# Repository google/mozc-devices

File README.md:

Circuit diagrams and firmware source code for Gboard DIY keyboards, previously
known as Google Japanese Input / Gboard April Fools.

This is not an officially supported Google product.

# Products

Please refer to the README in each directory for more details.

<table>
<tr>
<td>

[Google 日本語入力 ドラムセットバージョン](https://archive.google/drumsetkeyboard/)<br>
[Google Japanese Input Drum set version](https://archive.google/drumsetkeyboard/)

変換の煩わしさを感じさせない思いどおりの日本語入力を提供します。

- [Announce](https://blog.google/intl/ja-jp/products/android-chrome-play/2010_04_google/)
- Release date: Apr 1, 2010
- Source: Not open source

</td>
<td>

[Google 日本語入力 モールスバージョン](http://www.google.co.jp/ime/-.-.html)<br>
[Google Japanese Input Morse version](http://www.google.co.jp/ime/-.-.html)

モールス符号で思いどおりの日本語入力

- [Promotional video](https://www.youtube.com/watch?v=u5AYb778pwA)
- [Announce](https://japan.googleblog.com/2012/04/google.html)
- [Technical details](http://googledevjp.blogspot.jp/2012/06/google.html)
- Release date: Apr 1, 2012
- Source: [/third_party/mozc-morse](./third_party/mozc-morse)

</td>
</tr>
<tr>
<td>

[Google 日本語入力 パタパタバージョン](http://www.google.co.jp/ime/patapata/)<br>
[Google Japanese Input Patapata version](http://www.google.co.jp/ime/patapata/)

もう、なにも覚える必要はありません。
押して離すだけの日本語入力。

- [Promotional video](https://www.youtube.com/watch?v=HzUDAaYMNsA)
- [Announce](https://japan.googleblog.com/2013/04/google-patapata.html)
- [Technical details](http://googledevjp.blogspot.jp/2013/10/google.html)
- Release date: Apr 1, 2013
- Source: [/third_party/mozc-flap](./third_party/mozc-flap)

</td>
<td>

[Google 日本語入力 マジックハンドバージョン](https://archive.google/ime/m9/)<br>
[Google Japanese Input Magic hand version](https://archive.google/ime/m9/)

マジックハンドでらくらく入力

- [Promotional video](https://www.youtube.com/watch?v=0u1zoaJYAmw)
- [Announce](https://blog.google/intl/ja-jp/products/android-chrome-play/2014_04_m9/)
- Release date: Apr 1, 2014
- Source: Not open source

</td>
</tr>
<tr>
<td>

[Google 日本語入力 ピロピロバージョン](https://www.google.co.jp/ime/___o/)<br>
[Google Japanese Input Piropiro version](https://www.google.co.jp/ime/___o/)

もうキーはいらない

- [Promotional video](https://www.youtube.com/watch?v=gAgOnQqyDz0)
- [Announce](https://japan.googleblog.com/2015/04/piropiro.html)
- Release date: Apr 1, 2015
- Source: [/mozc-piropiro](./mozc-piropiro)

</td>
<td>

[Google 日本語入力 物理フリックバージョン](https://www.google.co.jp/ime/furikku/)<br>
[Google Japanese Input Physical Flick version](https://www.google.co.jp/ime/furikku/)

さわれるフリック

- [Promotional video](https://www.youtube.com/watch?v=5LI1PysAlkU)
- [Announce](https://japan.googleblog.com/2016/04/furikku.html)
- Release date: Apr 1, 2016
- Source: [/mozc-furikku](./mozc-furikku)

</td>
</tr>
<tr>
<td>

[日本語入力 プチプチバージョン](https://landing.google.co.jp/ime/ooooo/)<br>
[Google Japanese Input Puchi Puchi version](https://landing.google.co.jp/ime/ooooo/)

空気のように、軽やかな入力。

- [Promotional video](https://www.youtube.com/watch?v=RkJZDvHMyTA)
- [Announce](https://japan.googleblog.com/2017/04/ooooo.html)
- Release date: Apr 1, 2017
- Source: [/third_party/mozc-puchi](./third_party/mozc-puchi)

</td>
<td>

[Gboard 物理手書きバージョン](https://landing.google.co.jp/tegaki/)<br>
[Gboard Physical Handwriting version](https://landing.google.co.jp/tegaki/)

新しいタイプの手書き入力。

- [Promotional video](https://www.youtube.com/watch?v=guJnFY1R4I0)
- [Announce](https://japan.googleblog.com/2018/04/tegaki.html)
- [Technical details](https://developers-jp.googleblog.com/2018/04/tegaki.html)
- Release date: Apr 1, 2018
- Source: [/mozc-nazoru](./mozc-nazoru)

</td>
</tr>
<tr>
<td>

[Gboard スプーン曲げバージョン](https://landing.google.co.jp/---o/)<br>
[Gboard Spoon Bending version](https://landing.google.co.jp/---o/)

タネも仕掛けもない、柔軟な入力。

- [Promotional video](https://www.youtube.com/watch?v=DeJY5d14qKs)
- [Announce](https://japan.googleblog.com/2019/04/mageru.html)
- Release date: Apr 1, 2019
- Source:
  - [/mozc-mageru](./mozc-mageru) for firmware, schematics, and PCB layout.
  - [/third_party/mozc-mageru](./third_party/mozc-mageru) for 3D model.

</td>
<td>

[Gboard 湯呑みバージョン](https://g.co/yunomi/)<br>
[Gboard yunomi version](https://g.co/yunomi/)

もう、おすしかない。

- [Promotional video](https://www.youtube.com/watch?v=20pC05yisRM)
- [Announce](https://japan.googleblog.com/2021/10/gboard.html)
- Release date: Oct 1, 2021
- Source: [/mozc-yunomi](./mozc-yunomi)

</td>
</tr>
<tr>
<td>

[Gboard 棒バージョン](https://g.co/____)<br>
[Gboard bar version](https://g.co/____)

キーの次はボーです。

- [Promotional video](https://www.youtube.com/watch?v=9G3DWHf1xX0)
- [Announce](https://japan.googleblog.com/2022/10/gboard-2022.html)
- Release date: Oct 1, 2022
- Source: [/mozc-bar](./mozc-bar)

</td>
<td>

[Gboard 帽バージョン](https://g.co/CAPS)<br>
[Gboard CAPS version](https://g.co/CAPS)

入力は、帽険だ。

- [Promotional video](https://www.youtube.com/watch?v=6vib77CUxNM)
- [Announce](https://japan.googleblog.com/2023/10/caps.html)
- Release date: Oct 1, 2023
- Source: [/mozc-caps](./mozc-caps)

</td>
</tr>
<tr>
<td>

[Gboard 両面バージョン](https://g.co/double-sided)<br>
[Gboard double sided version](https://g.co/double-sided)

表面かと思ったら裏面でした。

- [Promotional video](https://www.youtube.com/watch?v=EHqPrHTN1dU)
- [Announce](https://blog.google/intl/ja-jp/products/android-chrome-play/gboard-2024)
- Release date: Oct 1, 2024
- Source: [/mozc-doublesided](./mozc-doublesided)

</td>
<td>

[Gboard ダイヤルバージョン](./mozc-dial/README_ja.md)<br>
[Gboard Dial Version](./mozc-dial)

まるくおさめました。

- [Promotional video](https://youtu.be/BgdWyD0cBx4)
- [Announce](https://blog.google/intl/ja-jp/products/android-chrome-play/gboard-2025)
- Release date: Oct 1, 2025
- Source: [/mozc-dial](./mozc-dial)

</td>
</tr>
<tr>
<td>

[Gboard くるくる バージョン](./mozc-conveyorbelt/README_ja.md)<br>
[Gboard Conveyor Belt version](./mozc-conveyorbelt)

流れるような文字入力を

- [Promotional video](https://www.youtube.com/watch?v=DAn34l_YrUM)
- [Announce](https://blog.google/intl/ja-jp/products/android-chrome-play/gboard-2026/)
- Release date: Oct 1, 2026
- Source: [/mozc-conveyorbelt](./mozc-conveyorbelt)

</td>
<td>
</td>
</tr>
</table>

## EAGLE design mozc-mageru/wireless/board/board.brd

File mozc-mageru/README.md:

# Gboard Spoon Bending Version

This contains programs, schematics and board layouts for Gboard Spoon Bending Version, which was released on **Apr 1, 2019**.

This is not an officially supported Google product.

# Contents

Directory structure is as follows.

- wireless/
  - firmware/
    - Firmware for the wireless version. (coming soon)
  - board/
    - Schematic and PCB layout made by EAGLE.
- wired/
  - firmware/
    - Arduino sketch for the wired version.
- ../third_party/mozc-mageru/spoon_stl/
   - Spoon shape data for 3D printing.

# Wired Version

## The spoon

Print the spoon under /third_party/mozc-mageru/spoon_stl/ using a 3D printer.
This is an example design of a flexible spoon that has a slot to embed a
flex sensor into.
We have tried it with PLA, but it will probably work with ABS as well.

## Electronic circuit

- Arduino Micro
- 22k-ohm resistor
- Flex sensor: FS-L-0055-253-ST (Spectra Symbol)

```
    Arduino Micro

         5V ---[22k ohm]-------+
                               |
         A5 -------------------+
                               |
        GND ---[Flex sensor]---+
```

## How to use the firmware

1. Open the sketch on Arduino IDE.
2. Choose "Arduino/Genuino Micro" in the [Tools]-[Board] menu.
3. If you are making Japanse-hiragana version, add ```#define JAPANESE_``` to the first line of the sketch
4. Upload to board.

## Sensor calibration

1. Open Serial Monitor.
2. Send '!' once to disable key output.
3. (the home position, which decides when to commit a character)
   Bend the sensor slightly and send '0'. Make sure the LED turns off when the spoon is not bent by external force.
4. (the position for the first letter)
   Bend the sensor slightly a bit more and send '1'.
5. (the position for the last letter)
   Bend the sensor to the end and send '2'.
6. Send 'w' to save the configuration to EEPROM.
7. Send '!' again to enable key output, or reset the device.

# Wireless Version

Coming soon.

# License

```
Licensed under the Apache License, Version 2.0 (the "License"); you may
not use this file except in compliance with the License. You may obtain
a copy of the License at

    http://www.apache.org/licenses/LICENSE-2.0

Unless required by applicable law or agreed to in writing, software
distributed under the License is distributed on an "AS IS" BASIS,
WITHOUT WARRANTIES OR CONDITIONS OF ANY KIND, either express or implied.
See the License for the specific language governing permissions and
limitations under the License.
```

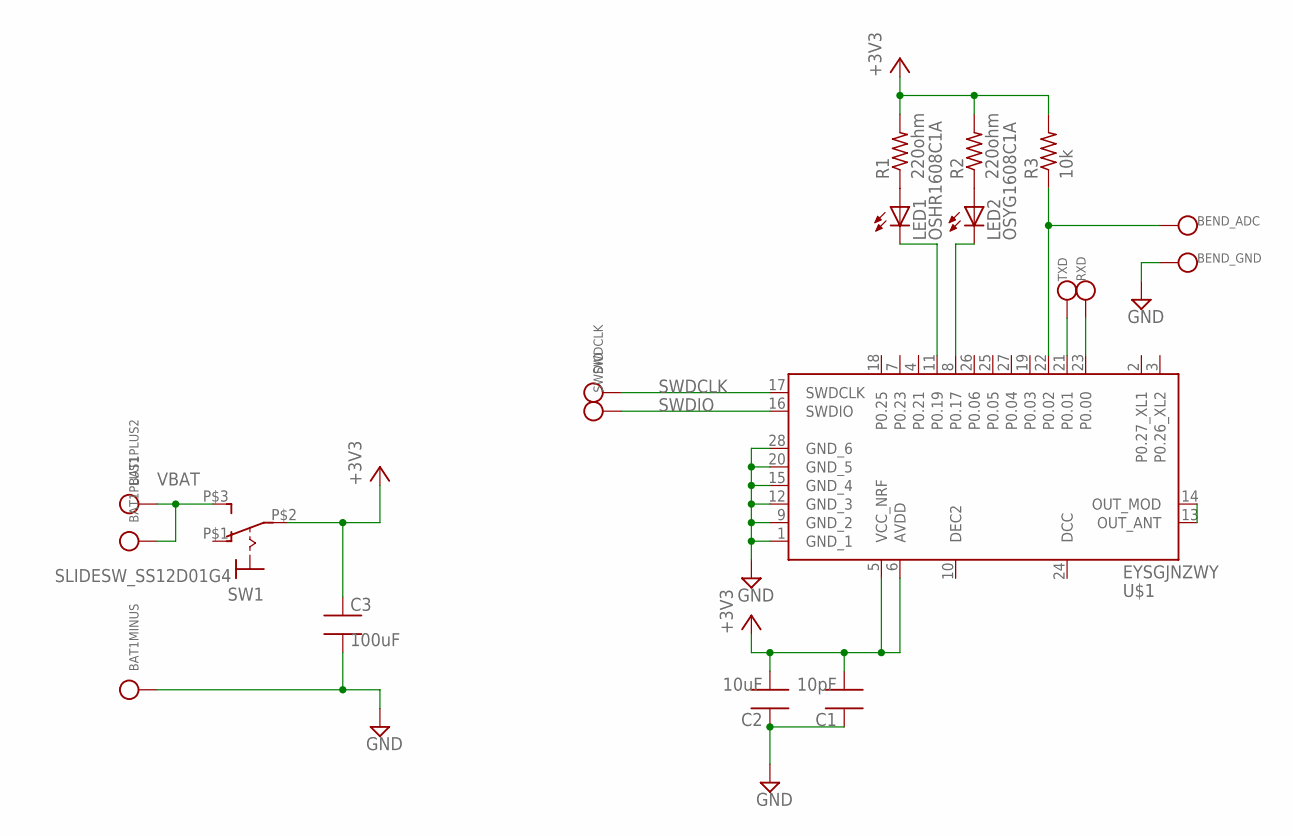
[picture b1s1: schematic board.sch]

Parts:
BAT1: BATTERY; CR1025
BEND_ADC: CHECK_PIN-SMD_100*60; SMD_100*60
BEND_GND: CHECK_PIN-SMD_100*60; SMD_100*60
C1: 10pF; 1005
C2: 10uF; 1005
C3: 100uF; 3216
LED1: OSHR1608C1A; 1608-LED
LED2: OSYG1608C1A; 1608-LED
R1, R2: 220ohm; 1608
R3: 10k; 1608
RXD: CHECK_PIN-SMD_100*60; SMD_100*60
SW1: SLIDESW_SS12D01G4; SS12D01G4
SWDCLK: CHECK_PIN-SMD_100*60; SMD_100*60
SWDIO: CHECK_PIN-SMD_100*60; SMD_100*60
TXD: CHECK_PIN-SMD_100*60; SMD_100*60
U$1: EYSGJNZWY; TAIYOYUDEN_BT_XXXXJN

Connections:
+3V3: C1.2, C2.2, C3.1, R1.2, R2.2, R3.2, SW1.P$2, U$1.5 (VCC_NRF), U$1.6 (AVDD)
GND: BAT1.-, BEND_GND.SIGNAL, C1.1, C2.1, C3.2, U$1.1 (GND_1), U$1.9 (GND_2), U$1.12 (GND_3), U$1.15 (GND_4), U$1.20 (GND_5), U$1.28 (GND_6)
unnamed: LED1.1 (A), R1.1
unnamed: LED2.1 (A), R2.1
unnamed: LED1.2 (K), U$1.11 (P0.19)
unnamed: U$1.13 (OUT_ANT), U$1.14 (OUT_MOD)
unnamed: LED2.2 (K), U$1.8 (P0.17)
unnamed: BEND_ADC.SIGNAL, R3.1, U$1.22 (P0.02)
RXD: RXD.SIGNAL, U$1.23 (P0.00)
SWDCLK: SWDCLK.SIGNAL, U$1.17 (SWDCLK)
SWDIO: SWDIO.SIGNAL, U$1.16 (SWDIO)
TXD: TXD.SIGNAL, U$1.21 (P0.01)
VBAT: BAT1.+_1, BAT1.+_2, SW1.P$3 (S)

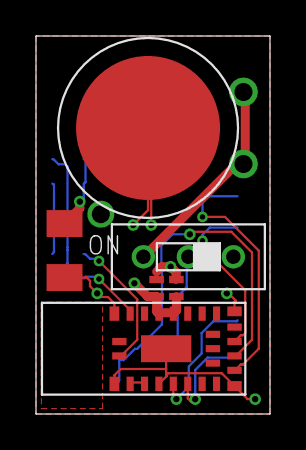
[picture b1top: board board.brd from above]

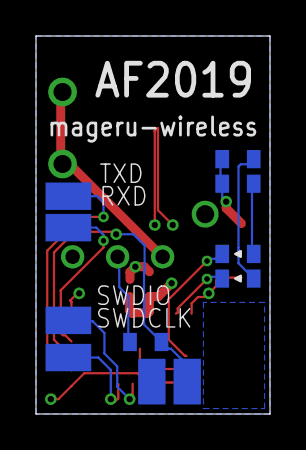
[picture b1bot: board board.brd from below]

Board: 4 copper layers, 13.0 x 21.0 mm, 17 parts (11 on the bottom side), 13 nets.

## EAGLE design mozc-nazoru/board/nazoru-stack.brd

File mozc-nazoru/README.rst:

Gboard Physical Handwriting Version
===================================

.. image:: https://badge.fury.io/py/nazoru-input.svg
   :target: https://pypi.python.org/pypi/nazoru-input/
   :alt: PyPi

Gboard Physical Handwriting Version is a device which translates your
scribble on your keyboard into a character. You can make your own Gboard
Physical Handwriting Version by printing your own printed circuit board
(PCB). Also, you can train your own model to recognize a customized set
of characters. This repository provides circuit diagram, the board
layout and software to recognize your stroke over the keyboard as a
character.

Software Usage
--------------

Install and Try
~~~~~~~~~~~~~~~~

Please make sure your local environemnt has packages as follows.

For Ubuntu/Debian:

.. code:: shell

  $ sudo apt install libffi-dev libcairo2 # For Ubuntu/Debian

For macOS:

.. code:: shell

  $ brew install cairo  # For macOS

After that, you can try nazoru-input after installing it from pip.

.. code:: shell

   $ pip install nazoru-input
   $ nazoru-input

Using ``nazoru-input``, You can make your own machine into an
input device which accepts scribbles on the connected keyboard and send
characters via bluetooth. At the beginning, this script scans
connected keyboards and starts listening to inputs from one of the
keyboards. Then it translates a sequence of keydowns into a predicted
character considering pressed timings, and send the character to the
target device paired by bluetooth.

If you want to try it for development, you can download the source from
github and use ``-e`` option.

.. code:: shell

   $ sudo apt install libffi-dev libcairo2 # For Ubuntu/Debian
   $ git clone https://github.com/google/mozc-devices.git
   $ cd mozc-devices/mozc-nazoru
   $ pip install -e .
   $ nazoru-input

Training Model
~~~~~~~~~~~~~~

.. code:: shell

   $ curl -LO https://github.com/google/mozc-devices/raw/master/mozc-nazoru/data/strokes.zip
   $ nazoru-training ./strokes.zip

We have a script to generate a trained model which recognizes input
characters from scribbles. This script renders input stroke data into
images to extract useful features for prediction considering position of
the key and timing of keyboard events. Rendered images are fed into the
neural network model and the optimizer tunes the model to fit the data.
Once the training is done, the script outputs the trained graph, which
you can use for your own device. In the case where you install
``nazoru-training`` from pip, you can find ``strokes.zip`` at here:
https://github.com/google/mozc-devices/blob/master/mozc-nazoru/data/strokes.zip

You can change some configurations by passing command line flags (e.g.
path to the input/output files, hyper-parameters). Run
``nazoru-training --help`` for details.

Hardware Setup
--------------

Printed Circuit Board
~~~~~~~~~~~~~~~~~~~~~
Gboard Physical Handwriting Version uses Raspberry Pi Zero for the
keyboard input recognition and RN42 module for Bluetooth connection to
your laptop. You can check the wiring at ``board/schematic.png``. Also,
the original CAD data in EAGLE format is available
(``board/nazoru-stack.sch`` and ``board/nazoru-stack.brd``). The board
has non-connected pads and connectors for SPI and I2C. The connector
itself should be compatible with other Raspberry Pi, but we tested it
only on Raspberry Pi Zero W.

.. image:: https://raw.githubusercontent.com/google/mozc-devices/master/mozc-nazoru/board/schematic.png
   :width: 1000px

Raspberry Pi Setup
~~~~~~~~~~~~~~~~~~

**Step 0 - Prepare your Raspberry Pi**

Please prepare your Raspberry Pi, SD card initialized by RASPBIAN
image, and RN42 module. Connect your Raspberry Pi with RN42 as the
schematic shows. Please make sure you can have access to the internet
and also it has enough disk space to install packages on the following
steps.

**Step 1 - Setup UART to RN42**

If you try it on Raspberry Pi Zero W or Raspberry Pi 3, you need to
have additional settings for the serial communication because they
equipped a wireless module connected by the UART. See details at `an
official document
<https://www.raspberrypi.org/documentation/configuration/uart.md>`_.
In short, you need to add ``enable_uart=1`` to ``/boot/config.txt`` on
your Raspberry Pi.

**Step 2 - Initial setup for RN42**

You need to write your initial setup to RN42. At first, install screen
and open ``/dev/serial0`` for configuration.

.. code:: shell

  $ sudo apt install screen
  $ sudo screen /dev/serial0 115200

After that, please type the following commands. Note that you need to
type ENTER after input commands. For example, please type ``$$$``
and ENTER to execute ``$$$`` command.

1. ``$$$`` : Get into the command mode. The green LED will blink
   faster.
2. ``+`` : You can see what you type.
3. ``SD,0540`` : Set the device class to keyboard.
4. ``S~,6`` : Set the profile to HID.
5. ``SH,0200`` : Set the HID flag to keyboard.
6. ``SN,nazoru-input`` : Set the device name as nazoru-input. You
   can name it as you want.
7. ``R,1`` : Reboot RN42.

You can quit the screen by ``C-a k``.

**Step 3 - Download and install nazoru-input**

We provide a service file at ``data/nazoru.service`` to launch
``nazoru-input`` when booting. You can install it by uncomment
``data_files`` entry in ``setup.py``. Also, before installing this
package, We'd strongly recommend you to install some  package from apt
repository as follows, so that you can install pre-built packages.

.. code:: shell

  $ sudo apt install git python-pip python-numpy python-cairocffi \
    python-h5py python-imaging python-scipy libblas-dev liblapack-dev \
    python-dev libatlas-base-dev gfortran python-setuptools \
    python-html5lib
  $ sudo pip install http://ci.tensorflow.org/view/Nightly/job/nightly-pi-zero/219/artifact/output-artifacts/tensorflow-1.6.0-cp27-none-any.whl
  $ git clone https://github.com/google/mozc-devices
  $ cd mozc-devices/mozc-nazoru
  $ vi setup.py  # Remove '#' for data_files to install nazoru.service.
  $ sudo pip install . # If you want to develop nazoru-input, please use 'sudo pip install -e .' instead.

**Step 4 - Enjoy!**

.. code:: shell

  $ sudo nazoru-input # If you miss sudo, nazoru-input may use a DummyBluetooth object.

Training Data Format
--------------------

We are providing the raw training data at ``data/strokes.zip``. Once you
uncompress the zip file, you will get a ``.ndjson`` file which contains
all entries (we call them **strokes**) we have used for training.

Each stroke entry contains the following field:

+----------+-----------+-------------------------------------------+
| Key      | Type      | Description                               |
+==========+===========+===========================================+
| id       | integer   | A unique identifier across all strokes.   |
+----------+-----------+-------------------------------------------+
| writer   | string    | A unique identifier of writer.            |
+----------+-----------+-------------------------------------------+
| kana     | string    | Label of the character drawn.             |
+----------+-----------+-------------------------------------------+
| events   | list      | List of keyboard events.                  |
+----------+-----------+-------------------------------------------+

Each event is a 3-tuple of (``key``, ``event type``, ``time``). ``key``
describes the key on which the event happened. ``event type`` describes
what type of event happened. It should be "down" (keydown) or "up"
(keyup). ``time`` describes the consumed time until the event is fired
in millisecond.

For example, the entry below denotes a stoke of "ほ
(\\u307b)" accompanied with a sequence of keyboard events
starting from the keydown event on "t" and ending at the keyup event on
"l" which was fired 1.005 seconds later after it started recording.

.. code:: json

    {
      "id": 5788999721418752,
      "writer": "ffb0dac6b8be3faa81da320e29a2ba72",
      "kana": "\u307b",
      "events": [
        ["t", "down", 0],
        ["g", "down", 40],
        ...
        ["l", "down", 966],
        ["l", "up", 1005]
      ]
    }

You can also prepare your own dataset in ``.ndjson`` format and rebuild
the model on it. The list of kanas to recognize is in
``src/nazoru/lib.py``. You can update that if you want to modify the set
of characters.

Network Structure
-----------------

Data Preprocessing
~~~~~~~~~~~~~~~~~~

Each stroke entry is rendered to a square image before any training
runs. The script (``nazoru-training``) renders strokes in various ways
to extract useful features. Our default settings extract 10 features
from each stroke entry: 8 directional features and 2 temporal features
on 16x16 square canvas; this means that the input shape is 16x16x10 by
default.

Convolutional Network
~~~~~~~~~~~~~~~~~~~~~

Rendered inputs are fed into a convolutional neural network designed for
this task. Body structure looks like:

-  Convolutional layer (kernel size: 3x3, filter size: 32, stride: 2,
   activation: Relu)
-  Separatable convolutional layer (kernel size: 3x3, filter size: 64,
   stride: 1, activation: Relu)
-  Separatable convolutional layer (kernel size: 3x3, filter size: 128,
   stride: 2, activation: Relu)
-  Separatable convolutional layer (kernel size: 3x3, filter size: 128,
   stride: 1, activation: Relu)

For more details about the separatable convolutional layers, please
refer to `MobileNet <https://arxiv.org/abs/1704.04861>`__ architecture.

Authors
-------

Machine Learning:
Shuhei Iitsuka <tushuhei@google.com>

Hardwares, system setups:
Makoto Shimazu <shimazu@google.com>

License
-------

Licensed under the Apache License, Version 2.0 (the "License"); you may
not use this file except in compliance with the License. You may obtain
a copy of the License at

    http://www.apache.org/licenses/LICENSE-2.0

Unless required by applicable law or agreed to in writing, software
distributed under the License is distributed on an "AS IS" BASIS,
WITHOUT WARRANTIES OR CONDITIONS OF ANY KIND, either express or implied.
See the License for the specific language governing permissions and
limitations under the License.

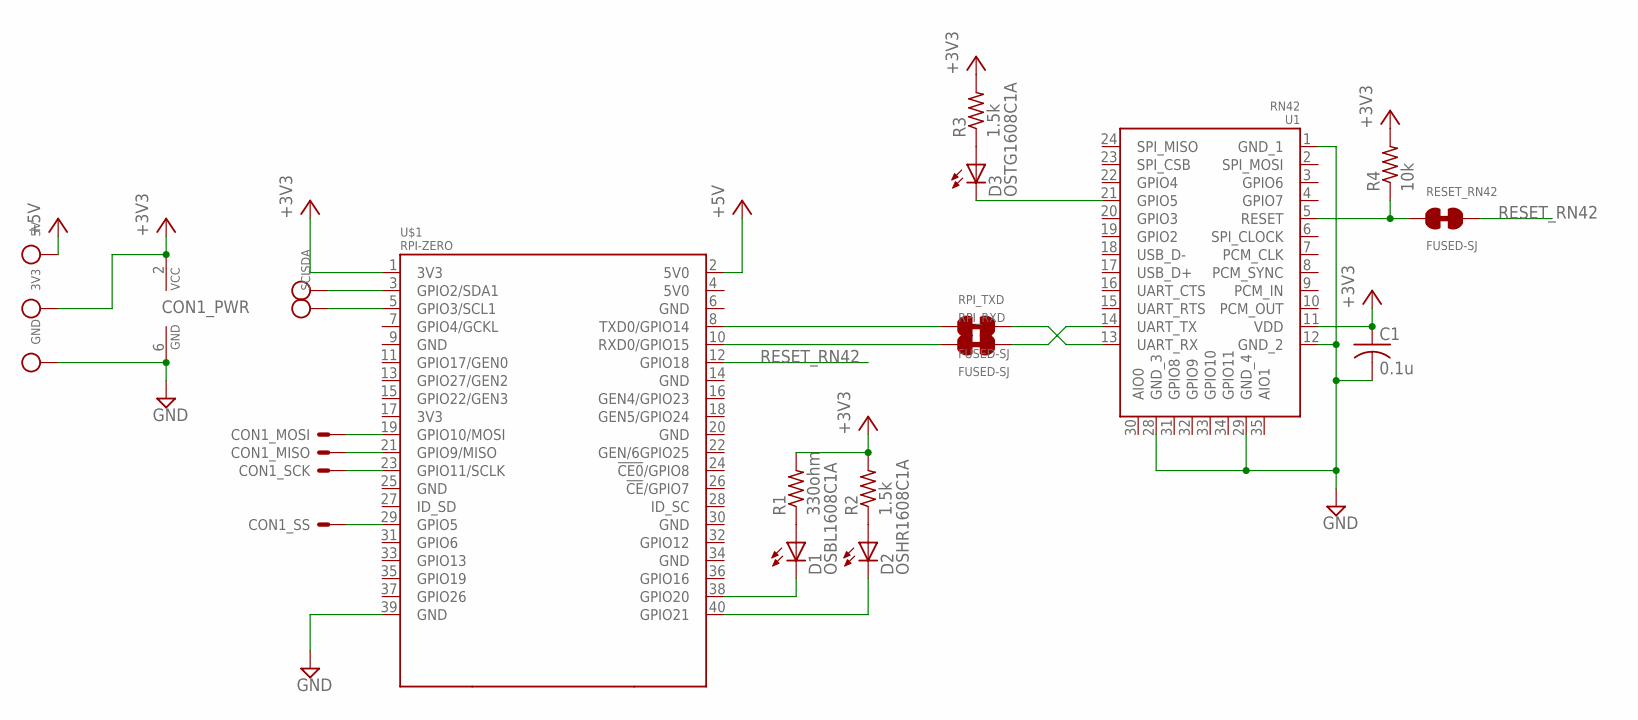
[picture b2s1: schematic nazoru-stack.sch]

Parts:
3V3, 5V: CHECK_PIN; SLC-22-G
C1: 0.1u; 2012-C
CON1: SPI; ML6
D1: OSBL1608C1A; 1608-LED
D2: OSHR1608C1A; 1608-LED
D3: OSTG1608C1A; 1608-LED
GND: CHECK_PIN; SLC-22-G
R1: 330ohm; 1608
R2, R3: 1.5k; 1608
R4: 10k; 1608
RESET_RN42: FUSED-SJ
RPI_RXD: FUSED-SJ
RPI_TXD: FUSED-SJ
SCL: CHECK_PIN; SLC-22-G
SDA: CHECK_PIN; SLC-22-G
U1: RN42
U$1: RPI-ZERO

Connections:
+3V3: 3V3.SIGNAL, C1.1, CON1.2 (VCC), R1.2, R2.2, R3.2, R4.2, U1.11 (VDD), U$1.1 (3V3)
+5V: 5V.SIGNAL, U$1.2 (5V0)
GND: C1.2, CON1.6 (GND), GND.SIGNAL, U1.1 (GND_1), U1.12 (GND_2), U1.28 (GND_3), U1.29 (GND_4), U$1.39 (GND)
unnamed: D1.1 (A), R1.1
unnamed: RPI_TXD.1, U$1.8 (TXD0/GPIO14)
unnamed: RPI_RXD.1, U$1.10 (RXD0/GPIO15)
unnamed: RPI_TXD.2, U1.13 (UART_RX)
unnamed: RPI_RXD.2, U1.14 (UART_TX)
unnamed: D1.2 (K), U$1.38 (GPIO20)
unnamed: D2.2 (K), U$1.40 (GPIO21)
unnamed: D2.1 (A), R2.1
unnamed: D3.1 (A), R3.1
unnamed: D3.2 (K), U1.21 (GPIO5)
unnamed: R4.1, RESET_RN42.1, U1.5 (RESET)
unnamed: CON1.4 (S), U$1.19 (GPIO10/MOSI)
unnamed: CON1.1 (S), U$1.21 (GPIO9/MISO)
unnamed: CON1.3 (S), U$1.23 (GPIO11/SCLK)
unnamed: CON1.5 (S), U$1.29 (GPIO5)
unnamed: SDA.SIGNAL, U$1.3 (GPIO2/SDA1)
unnamed: SCL.SIGNAL, U$1.5 (GPIO3/SCL1)
RESET_RN42: RESET_RN42.2, U$1.12 (GPIO18)

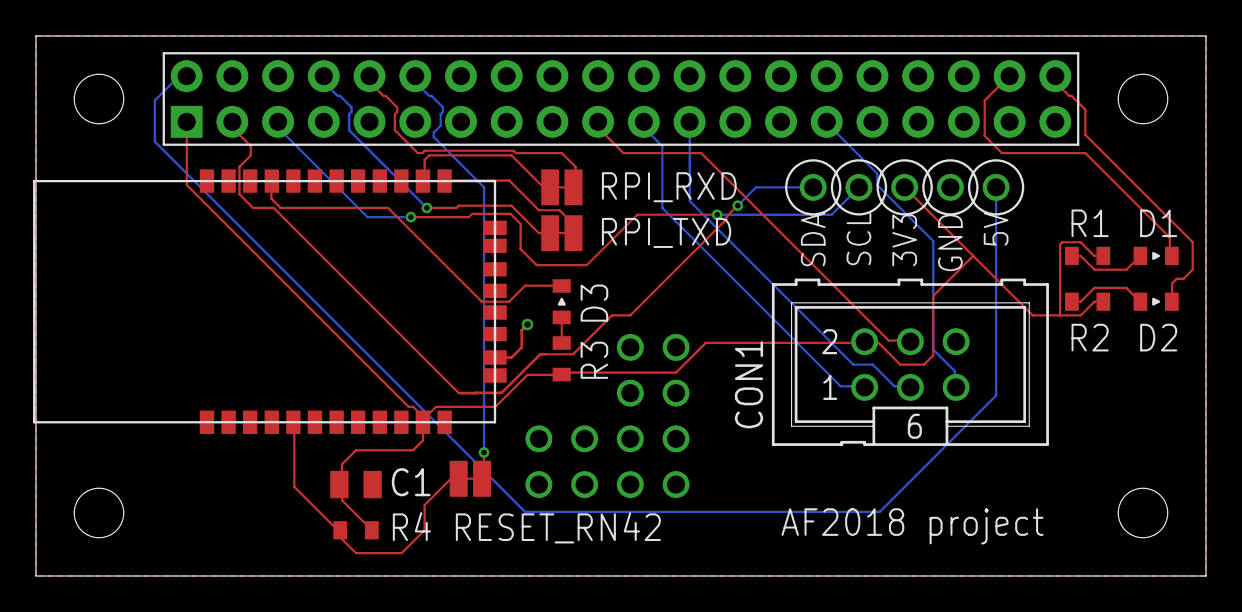
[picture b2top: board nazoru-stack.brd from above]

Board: 2 copper layers, 65.0 x 30.0 mm, 19 parts (0 on the bottom side), 21 nets.

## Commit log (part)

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2012-04-16 Initial directory structure.
2012-06-06 Initial upload of the Mozc-morse project.
2013-04-19 Initial upload of the Patapata input device firmware. Moving Morse key files to mozc-morse/ directory.
2013-04-19 Addition of a Readme file at the top level directory.
2015-03-25 Migrating wiki contents from Google Code
2015-03-25 Rename ProjectHome.md to README.md
2015-03-31 Fix a typo in README.
2015-03-31 Initial checkin of piropiro version.
2015-04-01 Add "ra" column to the input character list.
2015-04-03 Revise README to remove some redundancy. Add a photo of example device for assembly reference.
2015-06-11 Fixed 2 non-manifold STL data which were not able to 3D print themselves
2015-08-06 Add CONTRIBUTING file.
2015-08-10 Update STL files. - mesh density adjustment to improve precision - re-orientation to facilitate 3D printing - removal of unnecessary faces to prevent non-manifold errors
2016-03-31 Initial upload of the Physical Flick keyboard files.
2016-04-01 Add MCP3208 to the electronic parts list.
2016-04-01 Add some photos of an example device for reference.
2016-04-13 Add file.
2016-04-14 Fixed.
2016-04-22 Keytable update.
2016-04-26 Add some files.
2016-04-28 Add README.md
2017-03-28 Cleaned up the licensing.
2017-03-31 mozc-puchi upload
    mozc-puchi files are uploaded.
2017-03-31 latest readme
    updated and changed UTF-8
2017-03-31 license changed
    fixed
2017-03-31 fixed
    fixed
2017-03-31 back to original
    back to original
2017-03-31 Add puchi-puchi version.
2017-12-15 README.md: Fix typo
2018-03-08 Renamed
2018-03-31 Add nazoru-input in mozc-nazoru/
2018-03-31 Update the path to the schematic
2018-04-02 Update README.rst
    - Explicitly install nazoru-input from PyPi.
    - Remove unnecessary indents
    - apt install for necessary packages (tested on a fresh Debian 9 image on GCE).
2018-04-04 Specify encoding in reading README.rst from setup.py.
2018-04-04 Use directional and temporal features by default.
2018-04-04 Add PyPi badge in README.
2018-06-26 Shorten the wait time.
2018-08-03 Shorten the waiting time until inference
2018-08-03 Add a LED for chassis
2018-08-03 Make it work not on raspberry pi
2018-08-03 Change the brightness
2018-08-03 Add a LED in chassis (#18)
    LED was equipped in the chassis. This patch turns it on.
    SlowLED changes the brightness gradually. wiringpi is used for it to leverage the hardware PWA equipped by Raspberry Pi.
2018-09-11 More consistent demo
2018-09-11 Read ANSI escape codes by KeyboardRecorderFromConsole
2018-09-11 Add DELETE
2018-09-11 Move filterwarnings to the top and surpress FutureWarning too
2018-09-12 Refresh CLI output by input.
2019-03-31 add a newline
2019-03-31 Add mozc-mageru/ for Gboard Spoon Bending Version
2019-04-07 Remove wiringpi from OSX dependency
2019-04-09 Fix dependent module versions
2019-08-03 Add command to enable/disable key output.
    This function is needed for preventing the device from submitting serial
    commands by itself during calibration.
2020-12-02 Upgrade TensorFlow to 1.15.4
2021-09-16 Update TF version
2021-09-30 Add mozc-yunomi for Gboard Yunomi Version.
2021-10-01 Add link to Gboard yunomi version blog post.
2021-10-04 Rename board directories and add mount hole in base-pcb.
2021-10-08 Add silk-screen for USB connector pin assignment.
2021-11-15 Add yunomi base board for promicro.
2021-12-08 Update firmware to support promicro.
2021-12-10 Fix bug.
2021-12-12 Fix key mapping for osakana.
2021-12-16 Add README for Pro Micro
2022-06-06 Remove Kicad cache files
2022-06-06 TensorFlow version up
2022-10-01 Add mozc-bar for Gboard bar version.
2022-10-08 mozc-bar: Remove PCB shape from type-D case shape data.
    The shape of the PCB was merged into the STL data for type-D case by
    mistake.
2022-10-08 mozc-bar: Remove PCB shape from type-D shape data.
    The shape of the PCB was included in the case shape data for type-D case
    by mistake.
2023-03-23 This is a bug bounty test. Please ignore.. (rlciri)
2023-03-25 Update README.md
    PCB及びcaseの準備数がキーマップング画像とファームウェアと差異があったため修正
2023-03-27 [Mozc-bar] Fix length of the frame. (See #46 for details)
2023-04-09 Bug bounty test - please ignore.... (sbqxit)
2023-10-01 Add mozc-caps.
2023-10-09 Update mozc-caps.ino
    Implement the commit() function within the Compositor class. This function is designed to finalize the Japanese composition process by simulating the pressing of the Enter key, effectively submitting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
2024-09-30 Add mozc double sided version.
    Reviewed-by: Eliot Courtney <edcourtney@google.com>
2024-10-01 Fix links for flap and yunomi.
2024-10-01 Fix release date for puchi and nazoru
2024-10-01 Fix release date for magichand.
2024-10-01 Update mozc-doublesided/README.md to avoid unsupported syntax
2024-10-03 Add command to enable/disable key output. (#29)
    This function is needed for preventing the device from submitting serial
    commands by itself during calibration.
2024-10-04 Specify required Python versions to align with TF2.12
2024-12-21 Update README.md
    Fix spelling mistake.
2025-10-03 Fix link text for Gboard Dial Version
